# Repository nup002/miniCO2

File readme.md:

# MiniCO2

The MiniCO2 is a miniature USB-powered CO2 sensor that can be used 
anywhere you need a simple indicator of CO2. Its built-in LEDs light up green, orange, or red, depending on the 
amount of CO2 in the air. The default levels can be adjusted via software to suit your needs.

The image above is of a prototype. The final version will have a USB-C connector and wireless connectivity. 

## I want one!
The MiniCO2 is under development and cannot be purchased yet. But you can register your interest by adding your email
to the bottom of this form: https://docs.google.com/forms/d/e/1FAIpQLSczLEsP1Wsz9qHPjULFHvHtzbTa30NaE-r1zrS9D4k2iNyR5Q/viewform?usp=sf_link

Once finished, the MiniCO2 will be available for purchase on Tindie.

## Repo status
The repository is an active work in progress. Currently, only the KiCAD design files are provided. I intend to add:
 - CAD files for a 3D-printable enclosure
 - Firmware
 - Control application
 - Python example snippets on how to receive data

## Compatibility
The MiniCO2 will work with any standard USB type C port that can supply power. That means it can be plugged in nearly 
anywhere: Laptops, displays, chargers, battery banks, etc. It will also have wireless connectivity thanks to an 
ESP32-C6 module. This provides Wi-Fi, Bluetooth, Bluetooth Low Power, Thread, and Zigbee.

## Licenses
The MiniCO2 firmware is licensed under the GNU General Public License v3. The MiniCO2 hardware is licensed under 
CERN-OHL-S v2. This includes the PCB design files and enclosure design files. As an individual you are free to make your 
own MiniCO2, or to modify it, as long as these licenses are respected.

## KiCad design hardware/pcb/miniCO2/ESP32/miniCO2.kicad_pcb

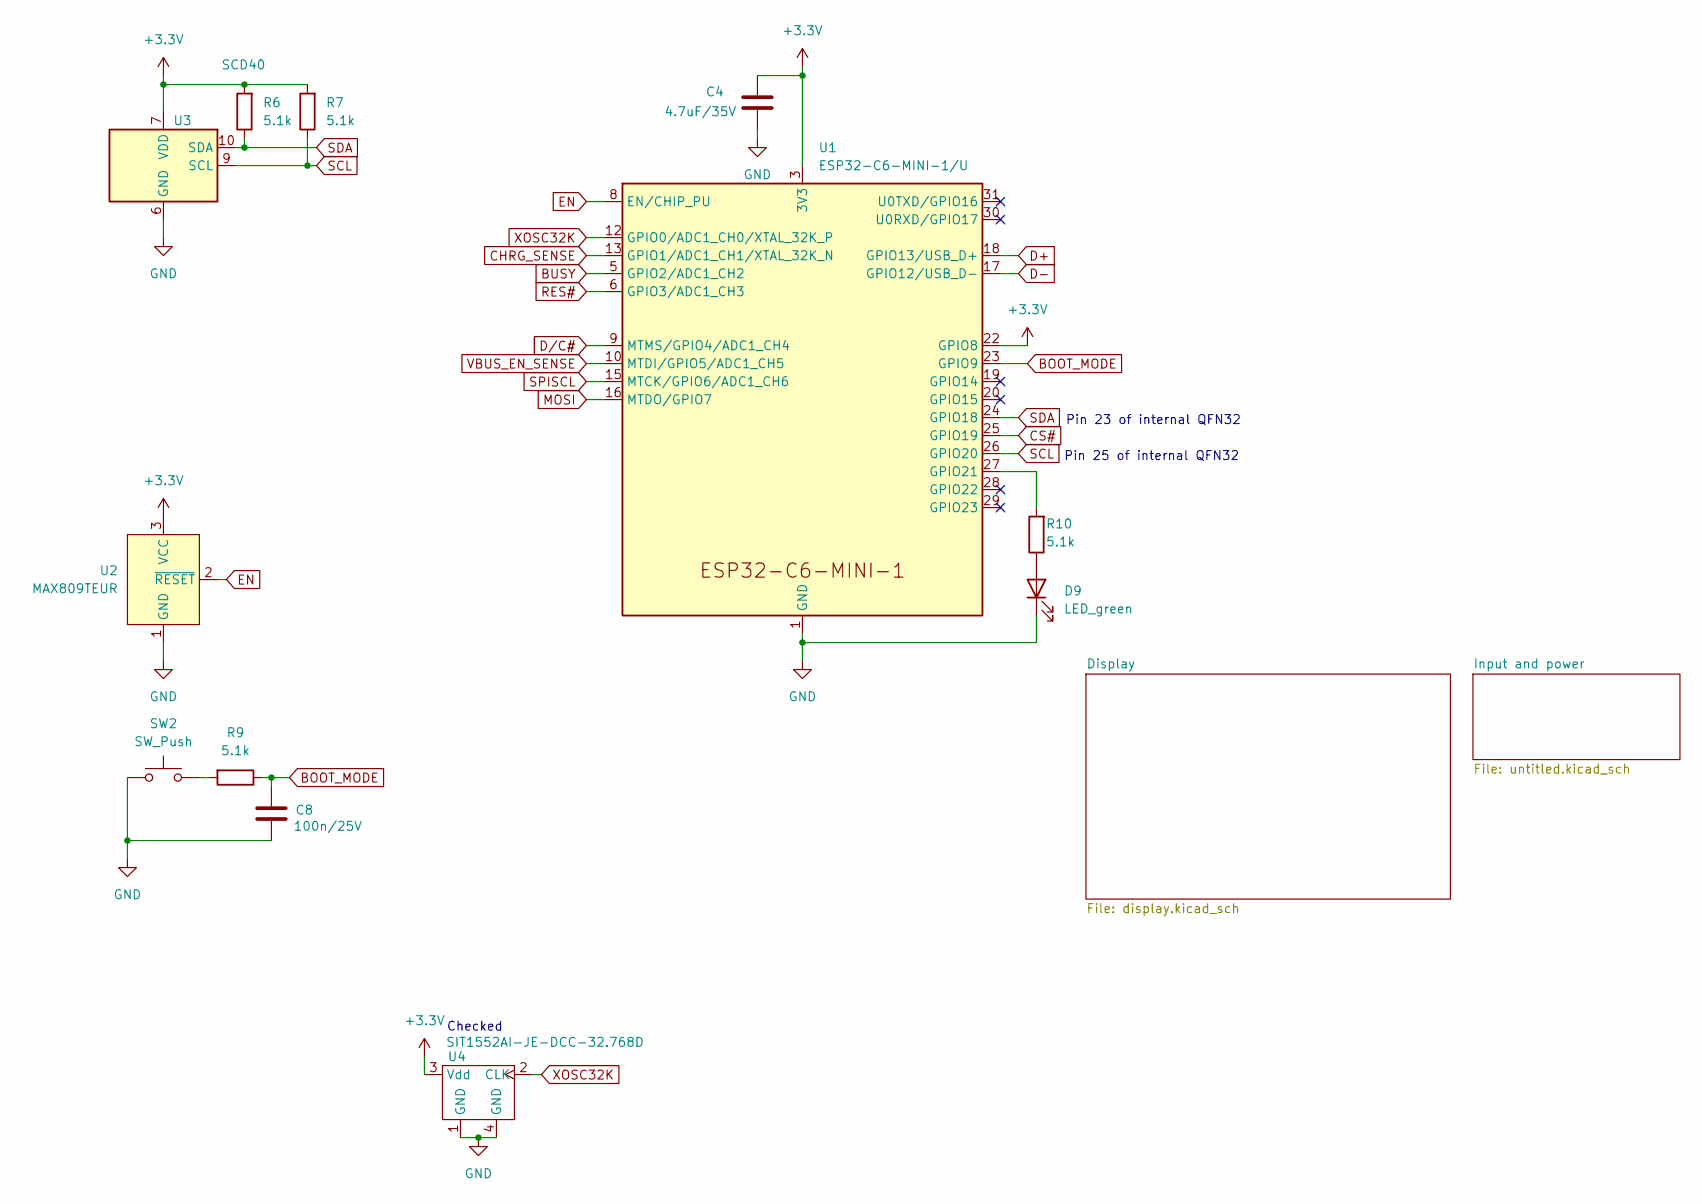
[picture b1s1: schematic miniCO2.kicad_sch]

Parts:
C4: 4.7uF/35V; C_0603_1608Metric; LCSC Part # C162274
C8: 100n/25V; C_0201_0603Metric; MPN 100nF 10% 10V 0402; LCSC Part # C181047
D9: LED_green; LED_0402_1005Metric; LCSC Part # C5336761
R6, R7, R9, R10: 5.1k; R_0201_0603Metric; LCSC Part # C270344
SW2: SW_Push; GT-TC108X-H034; LCSC Part # C22396279
U1: ESP32-C6-MINI-1/U; ESP32-C6-MINI-1; LCSC Part # C5736265
U2: MAX809TEUR; SOT-23; LCSC Part # C16711
U3: SCD40; Sensirion_SCD4x-1EP_10.1x10.1mm_P1.25mm_EP4.8x4.8mm; LCSC Part # C3037696
U4: SIT1552AI-JE-DCC-32.768D; SiT1552CSP_0.84x1.54; LCSC Part # C367054

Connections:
+3.3V: C4.2, R6.2, R7.2, U1.3 (3V3), U1.22 (GPIO8), U2.3 (VCC), U3.7 (VDD), U3.19 (VDD), U4.3 (Vdd); also elsewhere on the board
BOOT_MODE: C8.1, R9.1, U1.23 (GPIO9)
BUSY: U1.5 (GPIO2/ADC1_CH2); also elsewhere on the board
CHRG_SENSE: U1.13 (GPIO1/ADC1_CH1/XTAL_32K_N); also elsewhere on the board
CS#: U1.25 (GPIO19); also elsewhere on the board
D+: U1.18 (GPIO13/USB_D+); also elsewhere on the board
D-: U1.17 (GPIO12/USB_D-); also elsewhere on the board
D/C#: U1.9 (MTMS/GPIO4/ADC1_CH4); also elsewhere on the board
EN: U1.8 (EN/CHIP_PU), U2.2 (~RESET)
GND: C4.1, C8.2, D9.1 (K), SW2.1, U1.1 (GND), U1.2 (GND), U1.11 (GND), U1.14 (GND), U1.36 (GND), U1.37 (GND), U1.38 (GND), U1.39 (GND), U1.40 (GND), U1.41 (GND), U1.42 (GND), U1.43 (GND), U1.44 (GND), U1.45 (GND), U1.46 (GND), U1.47 (GND), U1.48 (GND), U1.49 (GND), U1.50 (GND), U1.51 (GND), U1.52 (GND), U1.53 (GND), U2.1 (GND), U3.6 (GND), U3.20 (GND), U3.21 (GND), U4.1 (GND), U4.4 (GND); also elsewhere on the board
MOSI: U1.16 (MTDO/GPIO7); also elsewhere on the board
unnamed: D9.2 (A), R10.1
unnamed: R9.2, SW2.2
unnamed: R10.2, U1.27 (GPIO21)
RES#: U1.6 (GPIO3/ADC1_CH3); also elsewhere on the board
SCL: R7.1, U1.26 (GPIO20), U3.9 (SCL)
SDA: R6.1, U1.24 (GPIO18), U3.10 (SDA)
SPISCL: U1.15 (MTCK/GPIO6/ADC1_CH6); also elsewhere on the board
VBUS_EN_SENSE: U1.10 (MTDI/GPIO5/ADC1_CH5); also elsewhere on the board
XOSC32K: U1.12 (GPIO0/ADC1_CH0/XTAL_32K_P), U4.2 (CLK)

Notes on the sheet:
Checked
Pin 23 of internal QFN32
Pin 25 of internal QFN32

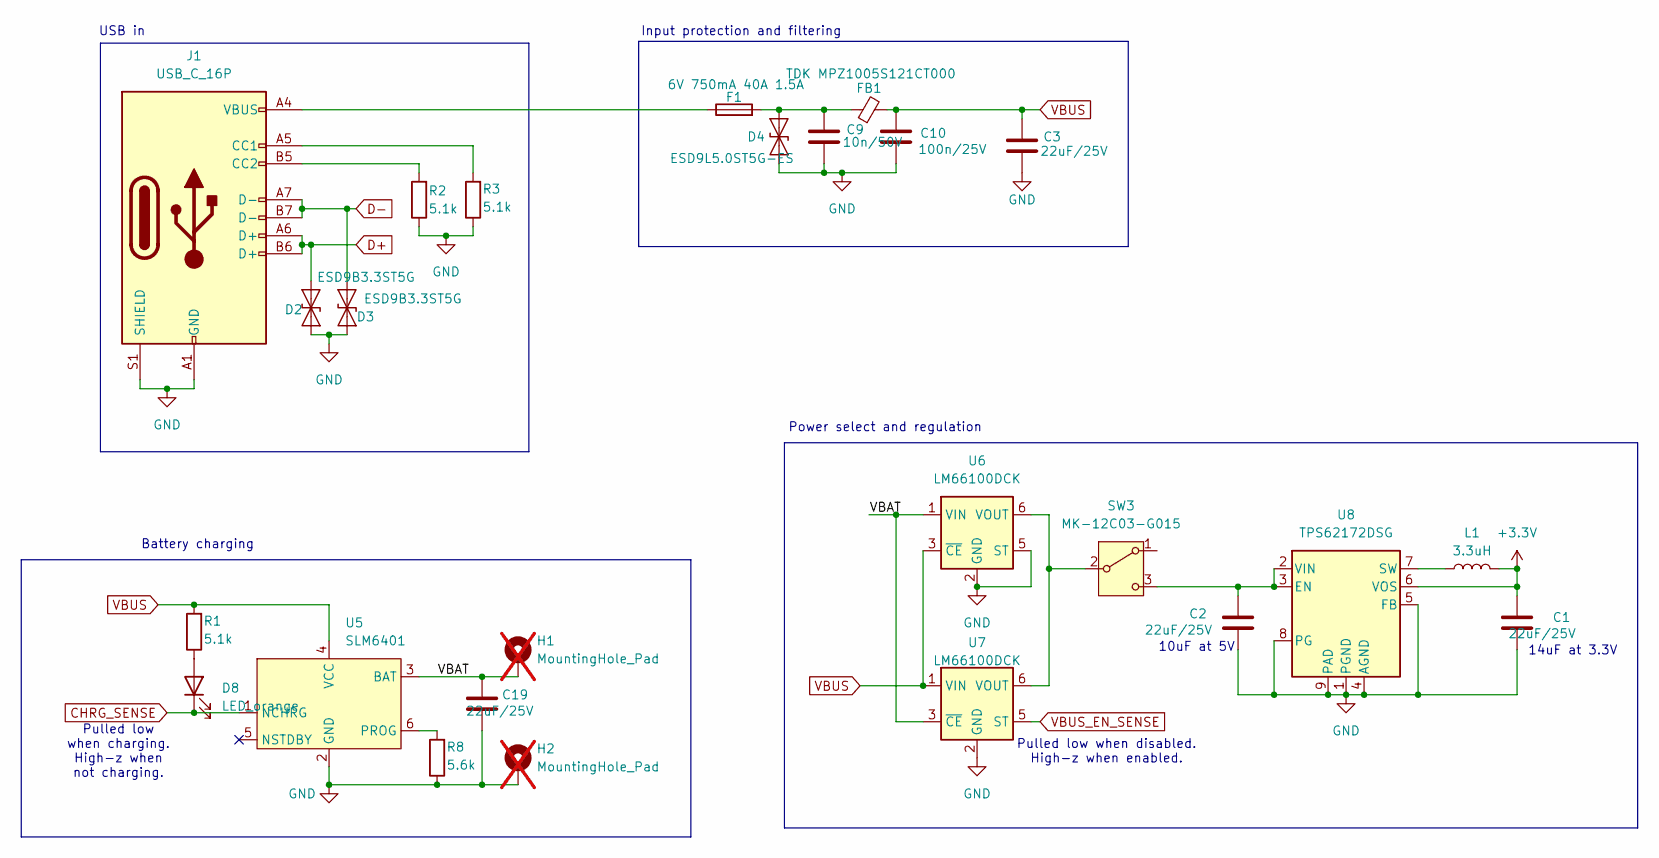
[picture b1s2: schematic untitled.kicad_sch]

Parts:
C1, C2, C3, C19: 22uF/25V; C_0805_2012Metric; LCSC Part # C6119899
C9: 10n/50V; C_0603_1608Metric; MPN 250V 10nF X7R ±10%; LCSC Part # C57112
C10: 100n/25V; C_0201_0603Metric; MPN 100nF 10% 10V 0402; LCSC Part # C181047
D2, D3: ESD9B3.3ST5G; D_SOD-923; LCSC Part # C96512
D4: ESD9L5.0ST5G-ES; D_SOD-923; LCSC Part # C5199180
D8: LED_orange; LED_0402_1005Metric; LCSC Part # C510300
F1: 6V 750mA 40A 1.5A; C_0402_1005Metric; LCSC Part # C5358567
FB1: TDK MPZ1005S121CT000; L_0402_1005Metric; LCSC Part # C107331
H1, H2: MountingHole_Pad; SolderWirePad_1x01_SMD_1x2mm; not fitted
J1: USB_C_16P; USB_C_Receptacle_G-Switch_GT-USB-7051x; LCSC Part # C2843970
L1: 3.3uH; L_Murata_LQH3NPZ; LCSC Part # C237449
R1, R2, R3: 5.1k; R_0201_0603Metric; LCSC Part # C270344
R8: 5.6k; R_0402_1005Metric; LCSC Part # C25908
SW3: MK-12C03-G015; LCSC Part # C2890358
U5: SLM6401; SOT-23-6; LCSC Part # C510627
U6, U7: LM66100DCK; SOT-363_SC-70-6; LCSC Part # C2869734
U8: TPS62172DSG; WSON-8-1EP_2x2mm_P0.5mm_EP0.9x1.6mm; LCSC Part # C59873

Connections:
+3.3V: C1.2, L1.2, U8.6 (VOS); also elsewhere on the board
/Input and power/VBAT: C19.2, H1.1, U5.3 (BAT), U6.1 (VIN), U7.3 (~CE)
CHRG_SENSE: D8.1 (K), U5.1 (NCHRG); also elsewhere on the board
D+: D2.2 (A2), J1.A6 (D+), J1.B6 (D+); also elsewhere on the board
D-: D3.2 (A2), J1.A7 (D-), J1.B7 (D-); also elsewhere on the board
GND: C1.1, C2.1, C3.1, C9.2, C10.2, C19.1, D2.1 (A1), D3.1 (A1), D4.1 (A1), H2.1, J1.A1 (GND), J1.A12 (GND), J1.B1 (GND), J1.B12 (GND), J1.S1 (SHIELD), R2.1, R3.1, R8.1, U5.2 (GND), U6.2 (GND), U6.5 (ST), U7.2 (GND), U8.1 (PGND), U8.4 (AGND), U8.5 (FB), U8.8 (PG), U8.9 (PAD); also elsewhere on the board
unnamed: C9.1, D4.2 (A2), F1.2, FB1.1
unnamed: D8.2 (A), R1.1
unnamed: F1.1, J1.A4 (VBUS), J1.A9 (VBUS), J1.B4 (VBUS), J1.B9 (VBUS)
unnamed: J1.A5 (CC1), R3.2
unnamed: J1.B5 (CC2), R2.2
unnamed: SW3.2 (B), U6.6 (VOUT), U7.6 (VOUT)
unnamed: C2.2, SW3.3 (C), U8.2 (VIN), U8.3 (EN)
unnamed: R8.2, U5.6 (PROG)
unnamed: L1.1, U8.7 (SW)
VBUS: C3.2, C10.1, FB1.2, R1.2, U5.4 (VCC), U6.3 (~CE), U7.1 (VIN)
VBUS_EN_SENSE: U7.5 (ST); also elsewhere on the board

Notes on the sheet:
Power select and regulation
14uF at 3.3V
Pulled low when charging. High-z when not charging.
Input protection and filtering
Pulled low when disabled. High-z when enabled.
USB in
Battery charging
10uF at 5V

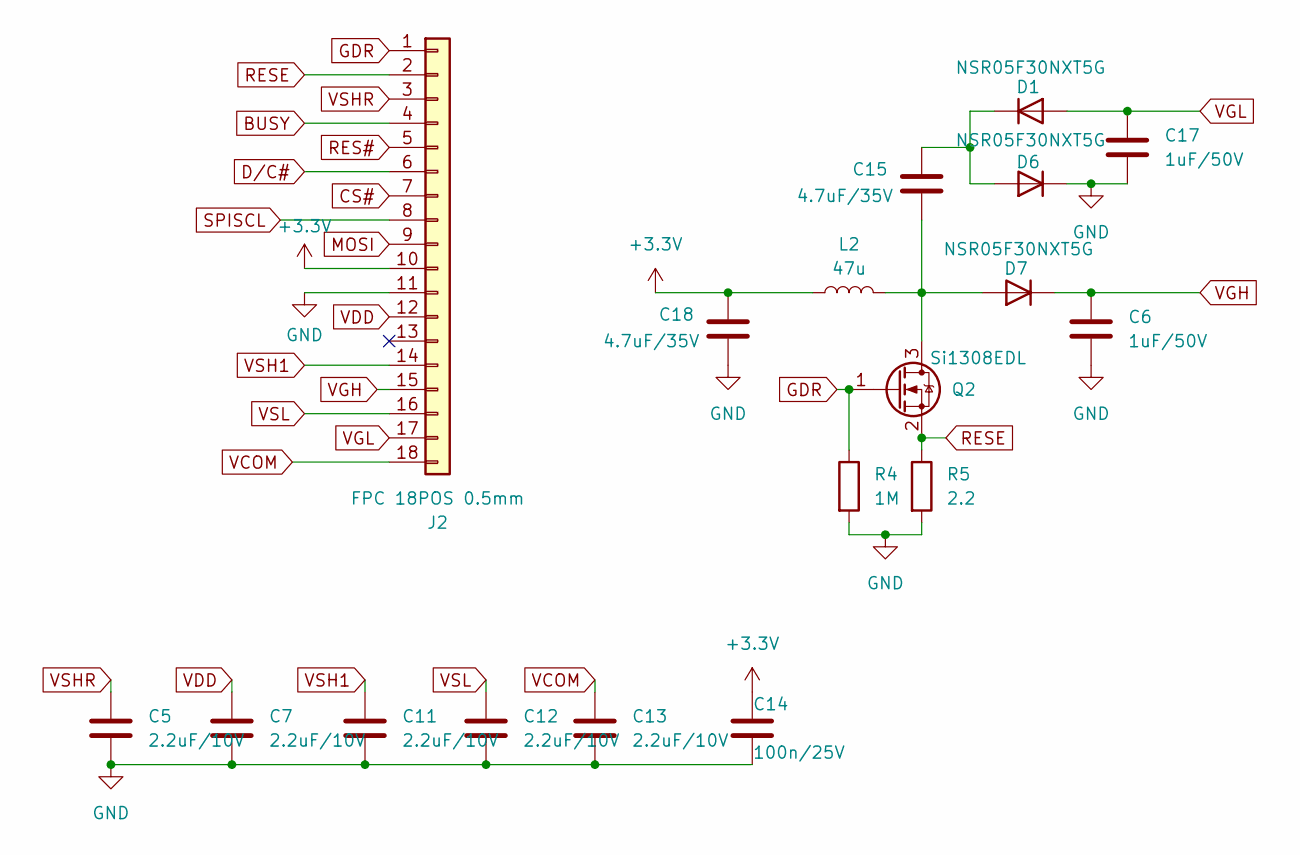
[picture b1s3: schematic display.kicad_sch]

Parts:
C5, C7, C11, C12, C13: 2.2uF/10V; C_0201_0603Metric; LCSC Part # C335106
C6, C17: 1uF/50V; C_0603_1608Metric; LCSC Part # C342951
C14: 100n/25V; C_0201_0603Metric; MPN 100nF 10% 10V 0402; LCSC Part # C181047
C15, C18: 4.7uF/35V; C_0603_1608Metric; LCSC Part # C162274
D1, D6, D7: NSR05F30NXT5G; XDFN-2(0.6x1); LCSC Part # C604339
J2: FPC 18POS 0.5mm; XKB Connection X05C2018TZ; LCSC Part # C397324
L2: 47u; L_SMD_2.2x1.6mm; LCSC Part # C961366
Q2: Si1308EDL; SOT-323_SC-70; LCSC Part # C7603347
R4: 1M; R_0201_0603Metric; LCSC Part # C473450
R5: 2.2; R_0201_0603Metric; LCSC Part # C270323

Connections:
+3.3V: C14.1, C18.2, J2.10, L2.1; also elsewhere on the board
BUSY: J2.4; also elsewhere on the board
CS#: J2.7; also elsewhere on the board
D/C#: J2.6; also elsewhere on the board
GDR: J2.1, Q2.1 (G), R4.1
GND: C5.1, C6.1, C7.1, C11.1, C12.1, C13.1, C14.2, C17.1, C18.1, D6.1 (K), J2.11, R4.2, R5.2; also elsewhere on the board
MOSI: J2.9; also elsewhere on the board
unnamed: C15.2, D1.1 (K), D6.2 (A)
unnamed: C15.1, D7.2 (A), L2.2, Q2.3 (D)
RES#: J2.5; also elsewhere on the board
RESE: J2.2, Q2.2 (S), R5.1
SPISCL: J2.8; also elsewhere on the board
VCOM: C13.2, J2.18
VDD: C7.2, J2.12
VGH: C6.2, D7.1 (K), J2.15
VGL: C17.2, D1.2 (A), J2.17
VSH1: C11.2, J2.14
VSHR: C5.2, J2.3
VSL: C12.2, J2.16

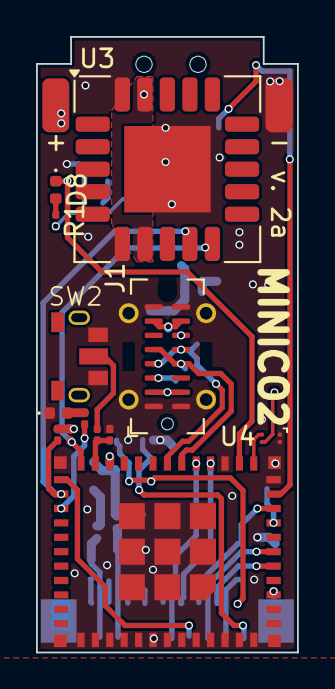
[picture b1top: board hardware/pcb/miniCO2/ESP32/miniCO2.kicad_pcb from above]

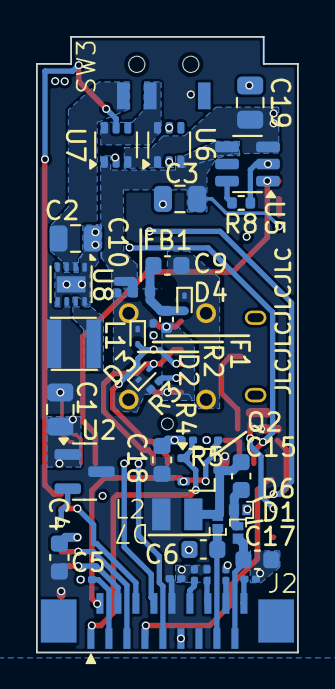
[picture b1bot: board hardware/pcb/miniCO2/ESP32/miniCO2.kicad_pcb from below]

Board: 4 copper layers, 14.5 x 34.2 mm, 55 parts (40 on the bottom side), 42 nets.

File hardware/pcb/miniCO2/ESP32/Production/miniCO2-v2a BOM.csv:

"Designator","Reference","Footprint","LCSC Part #"
"U8","TPS62172DSG","Package_SON:WSON-8-1EP_2x2mm_P0.5mm_EP0.9x1.6mm","C59873"
"U6,U7","LM66100DCK","Package_TO_SOT_SMD:SOT-363_SC-70-6","C2869734"
"U5","SLM6401","Package_TO_SOT_SMD:SOT-23-6","C510627"
"U4","SIT1552AI-JE-DCC-32.768D","miniCO2:SiT1552CSP_0.84x1.54","C367054"
"U3","SCD40","miniCO2:Sensirion_SCD4x-1EP_10.1x10.1mm_P1.25mm_EP4.8x4.8mm","C3037696"
"U2","MAX809TEUR","Package_TO_SOT_SMD:SOT-23","C16711"
"U1","ESP32-C6-MINI-1/U","PCM_Espressif:ESP32-C6-MINI-1","C5736265"
"SW3","MK-12C03-G015","miniCO2:MK-12C03-G015","C2890358"
"SW2","SW_Push","miniCO2:GT-TC108X-H034","C22396279"
"R8","5.6k","Resistor_SMD:R_0402_1005Metric","C25908"
"R5","2.2","Resistor_SMD:R_0201_0603Metric","C270323"
"R4","1M","Resistor_SMD:R_0201_0603Metric","C473450"
"R1,R2,R3,R6,R7,R9,R10","5.1k","Resistor_SMD:R_0201_0603Metric","C270344"
"Q2","Si1308EDL","Package_TO_SOT_SMD:SOT-323_SC-70","C7603347"
"L2","47u","miniCO2:L_SMD_2.2x1.6mm","C961366"
"L1","3.3uH","miniCO2:L_Murata_LQH3NPZ","C237449"
"J2","FPC 18POS 0.5mm","miniCO2:XKB Connection X05C2018TZ","C397324"
"J1","USB_C_16P","miniCO2:USB_C_Receptacle_G-Switch_GT-USB-7051x","C2843970"
"FB1","TDK MPZ1005S121CT000","Inductor_SMD:L_0402_1005Metric","C107331"
"F1","6V 750mA 40A 1.5A","Capacitor_SMD:C_0402_1005Metric","C5358567"
"D9","LED_green","LED_SMD:LED_0402_1005Metric","C5336761"
"D8","LED_orange","LED_SMD:LED_0402_1005Metric","C510300"
"D4","ESD9L5.0ST5G-ES","Diode_SMD:D_SOD-923","C5199180"
"D2,D3","ESD9B3.3ST5G","Diode_SMD:D_SOD-923","C96512"
"D1,D6,D7","NSR05F30NXT5G","miniCO2:XDFN-2(0.6x1)","C604339"
"C9","10n/50V","Capacitor_SMD:C_0603_1608Metric","C57112"
"C8,C10,C14","100n/25V","Capacitor_SMD:C_0201_0603Metric","C181047"
"C6,C17","1uF/50V","Capacitor_SMD:C_0603_1608Metric","C342951"
"C5,C7,C11,C12,C13","2.2uF/10V","Capacitor_SMD:C_0201_0603Metric","C335106"
"C4,C15,C18","4.7uF/35V","Capacitor_SMD:C_0603_1608Metric","C162274"
"C1,C2,C3,C19","22uF/25V","Capacitor_SMD:C_0805_2012Metric","C6119899"

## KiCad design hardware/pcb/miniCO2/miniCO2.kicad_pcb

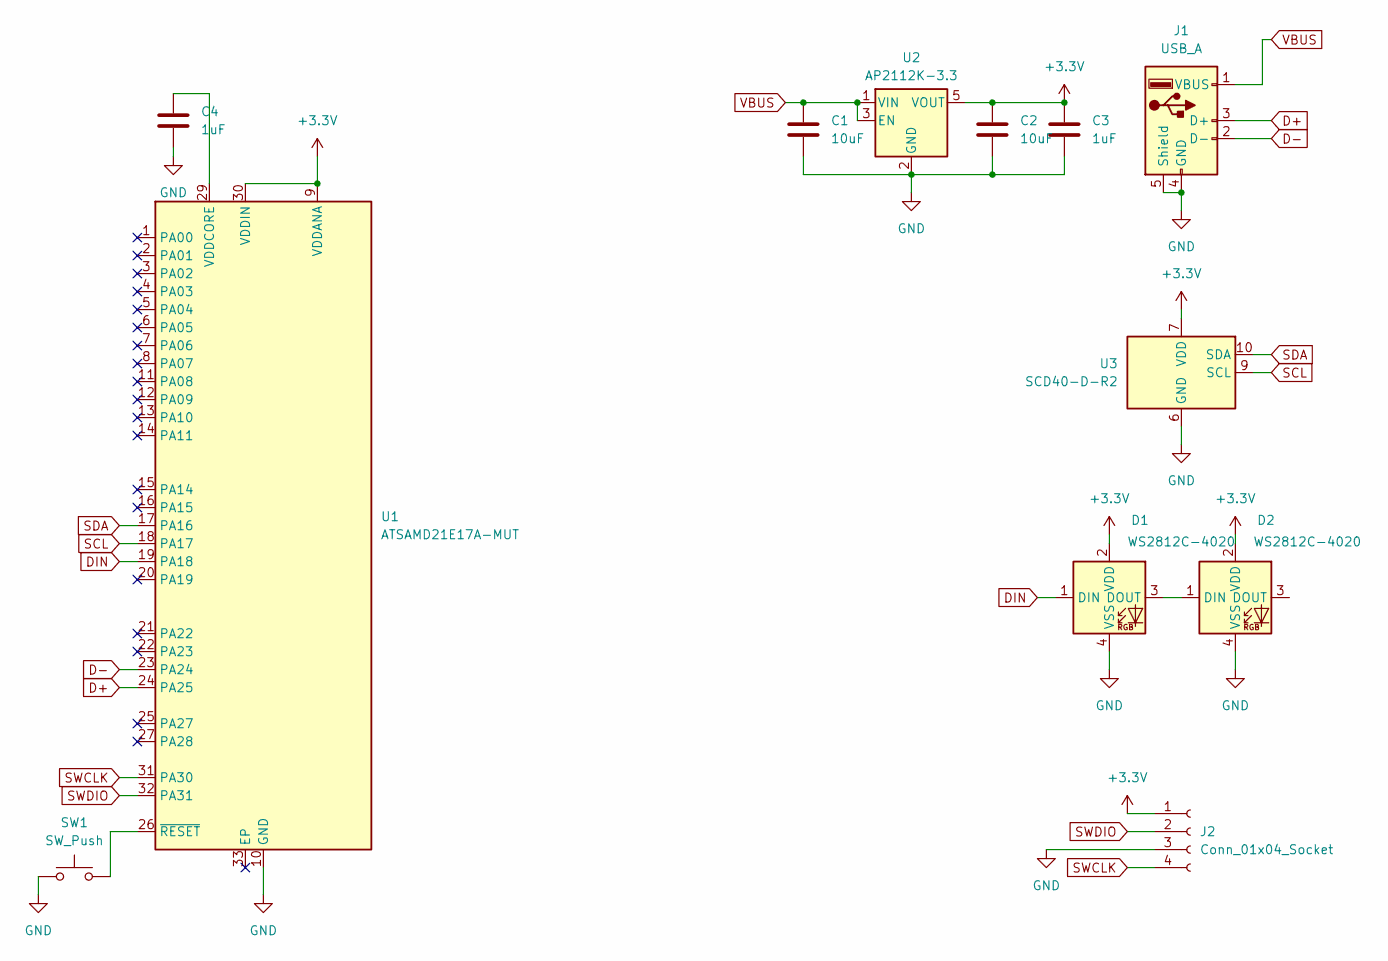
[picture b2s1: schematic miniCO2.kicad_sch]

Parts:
C1, C2: 10uF; C_0603_1608Metric; LCSC Part # C19702
C3, C4: 1uF; C_0402_1005Metric; LCSC Part # C5137485
D1, D2: WS2812C-4020; LCSC Part # C4154870
J1: USB_A; 917-P81A102ED60200; LCSC Part # C2763083
J2: Conn_01x04_Socket; SWD_pogo_pads
SW1: SW_Push; LS75C2D-T; LCSC Part # C962551
U1: ATSAMD21E17A-MUT; QFN-32-1EP_5x5mm_P0.5mm_EP3.6x3.6mm; LCSC Part # 3A991A2
U2: AP2112K-3.3; SOT-23-5; LCSC Part # C51118
U3: SCD40-D-R2; Sensirion_SCD4x-1EP_10.1x10.1mm_P1.25mm_EP4.8x4.8mm; LCSC Part # C3659421

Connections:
+3.3V: C2.2, C3.2, D1.2 (VDD), D2.2 (VDD), J2.1, U1.9 (VDDANA), U1.30 (VDDIN), U2.5 (VOUT), U3.7 (VDD), U3.19 (VDD)
D+: J1.3 (D+), U1.24 (PA25)
D-: J1.2 (D-), U1.23 (PA24)
DIN: D1.1 (DIN), U1.19 (PA18)
GND: C1.1, C2.1, C3.1, C4.1, D1.4 (VSS), D2.4 (VSS), J1.4 (GND), J1.5 (Shield), J2.3, SW1.1, U1.10 (GND), U1.28 (GND), U2.2 (GND), U3.6 (GND), U3.20 (GND), U3.21 (GND)
unnamed: D1.3 (DOUT), D2.1 (DIN)
unnamed: C4.2, U1.29 (VDDCORE)
unnamed: SW1.2, U1.26 (~RESET)
SCL: U1.18 (PA17), U3.9 (SCL)
SDA: U1.17 (PA16), U3.10 (SDA)
SWCLK: J2.4, U1.31 (PA30)
SWDIO: J2.2, U1.32 (PA31)
VBUS: C1.2, J1.1 (VBUS), U2.1 (VIN), U2.3 (EN)

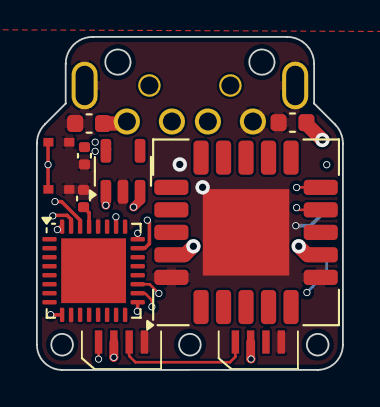
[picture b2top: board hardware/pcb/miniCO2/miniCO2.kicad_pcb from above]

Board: 4 copper layers, 17.0 x 18.5 mm, 12 parts (1 on the bottom side), 13 nets.

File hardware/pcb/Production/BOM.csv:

"Designator","Comment","Footprint","LCSC Part #"
"C1,C2","10uF","Capacitor_SMD:C_0603_1608Metric","C19702"
"C3,C4","1uF","Capacitor_SMD:C_0402_1005Metric","C5137485"
"D1,D2","WS2812C-4020","MiniCO2:WS2812C-4020","C4154870"
"J1","USB_A","MiniCO2:917-P81A102ED60200"," C2763083"
"J2","Conn_01x04_Socket","MiniCO2:SWD_pogo_pads",""
"SW1","SW_Push","MiniCO2:LS75C2D-T","C962551"
"U1","ATSAMD21E17A-MUT","MiniCO2:QFN-32-1EP_5x5mm_P0.5mm_EP3.6x3.6mm","C614305"
"U2","AP2112K-3.3","Package_TO_SOT_SMD:SOT-23-5","C51118"
"U3","SCD40-D-R2","MiniCO2:Sensirion_SCD4x-1EP_10.1x10.1mm_P1.25mm_EP4.8x4.8mm","C3659421"

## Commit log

2024-07-25 miniCO2 footprints
2024-07-25 Footprints and 3D models for components
2024-07-25 Routing finished
2024-07-26 Make prototype
2024-07-28 Version 1 finished
2024-07-29 Progress towards single-sided design
2024-07-29 Switch to front facing LEDs
2024-07-30 Version 1 finished and sent to production
2024-07-31 Fix D1, D2 footprints
2024-08-13 Readme and licenses
2024-08-13 Image
2024-08-13 Update readme.md
    Center image
2024-09-11 Version 1a
2024-09-26 scd40 centralization
    Centralize SCD40 (shifted by 100um).
    Bump version to 1b
2024-11-13 First commit of firmware
2024-11-14 Add queues
2024-11-15 Progress
    Fix queues, refactoring some files, more informative logs
2024-11-15 Implemented controller
2024-11-15 LED colors set from co2 level
2024-11-17 Pulsing LEDs, device state, and more error handling
2024-11-19 Fix enum to strings
2024-11-19 Port code to c++
2024-11-19 Implement BTHome
2024-11-19 BLE data transmission implemented
2024-11-20 Format serial output as json
2024-11-29 Add custom measurement interval
2024-11-29 Setting up zigbee support
2024-11-29 A bit more progress on zigbee
2024-11-30 Modifying zigbee code for temp&hum
2024-12-01 connecting the zigbee queue
2024-12-01 Add config structs
2024-12-01 LOGI string reformatting
2024-12-05 Add CO2 measurements to zigbee
2024-12-07 introduce console
2025-01-01 Basic console implemented
2025-01-02 Event loop finally working
2025-01-03 Configuration
2025-01-03 LED CO2 levels config
2025-02-02 LEd zigbee things
2025-02-16 First commit of version 2
2025-02-17 Modifications before sending to production
2025-03-09 version 2
2025-04-01 Switching to hot swap sockets
